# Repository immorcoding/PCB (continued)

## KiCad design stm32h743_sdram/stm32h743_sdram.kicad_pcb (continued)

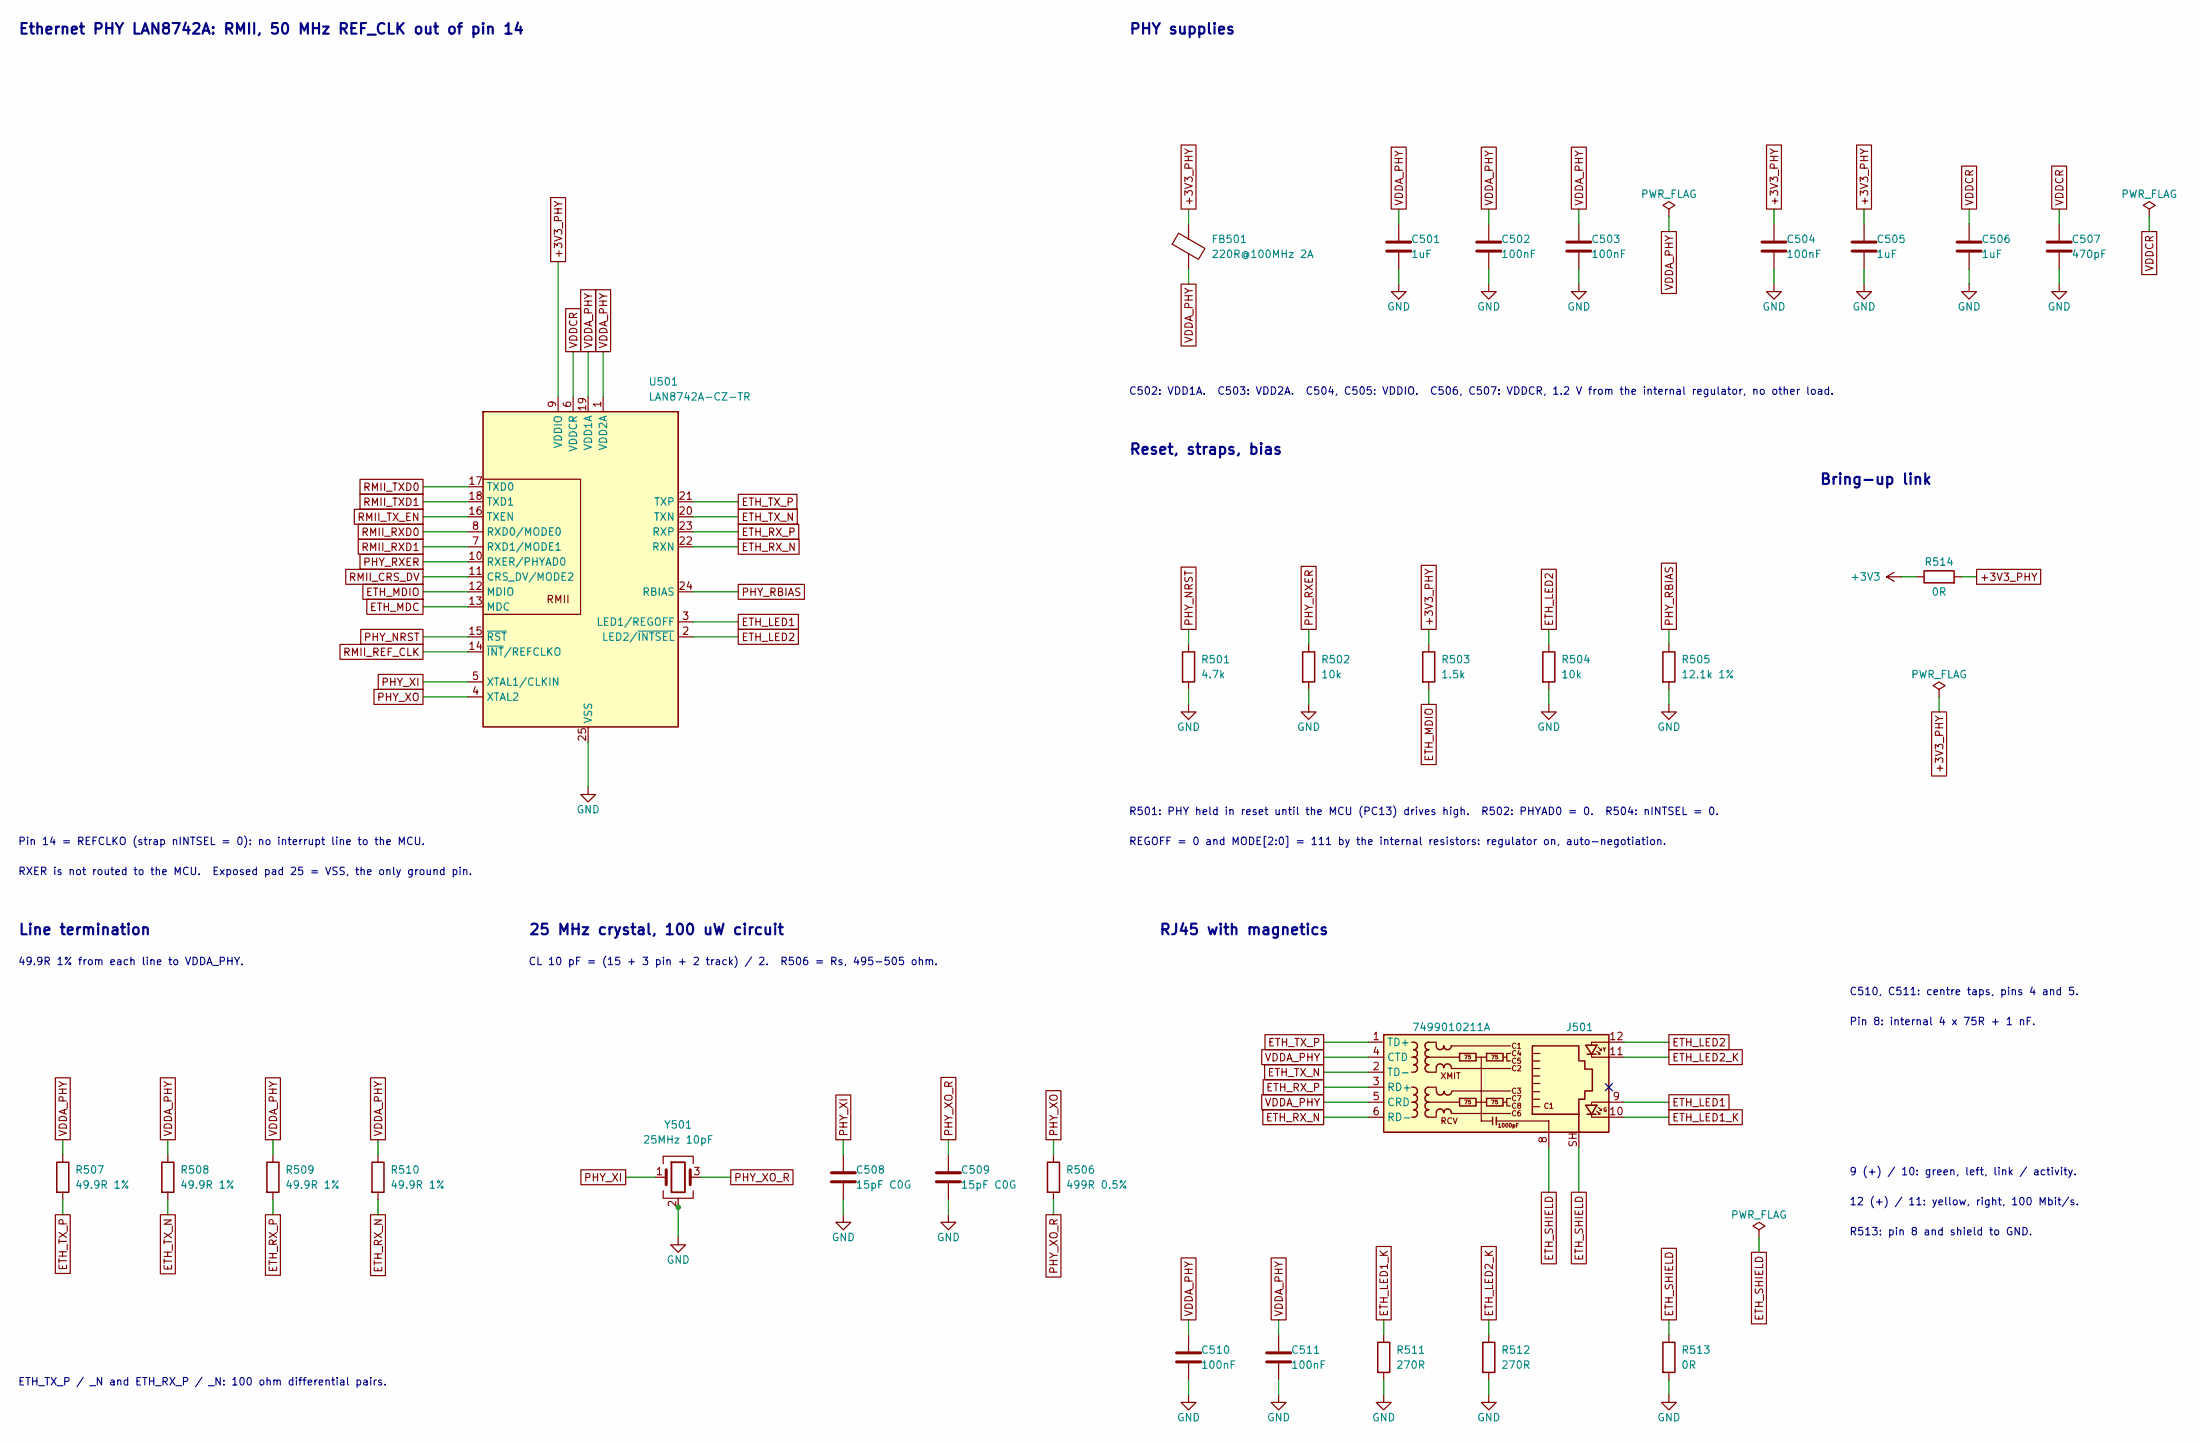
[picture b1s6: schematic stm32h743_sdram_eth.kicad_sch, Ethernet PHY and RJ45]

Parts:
C501, C505, C506: 1uF; C_0603_1608Metric
C502, C503, C504, C510, C511: 100nF; C_0402_1005Metric
C507: 470pF; C_0402_1005Metric
C508, C509: 15pF C0G; C_0402_1005Metric
FB501: 220R@100MHz 2A; L_0603_1608Metric; MPN MH1608-221Y
J501: 7499010211A; RJ45_Wuerth_7499010211A_Horizontal; MPN 7499010211A
R501: 4.7k; R_0402_1005Metric
R502, R504: 10k; R_0402_1005Metric
R503: 1.5k; R_0402_1005Metric
R505: 12.1k 1%; R_0402_1005Metric
R506: 499R 0.5%; R_0402_1005Metric
R507, R508, R509, R510: 49.9R 1%; R_0402_1005Metric
R511, R512: 270R; R_0402_1005Metric
R513: 0R; R_0805_2012Metric
R514: 0R; R_0805_2012Metric; Rating jumper, 2 A or more
U501: LAN8742A-CZ-TR; VQFN-24-1EP_4x4mm_P0.5mm_EP2.5x2.5mm_ThermalVias; MPN LAN8742A-CZ-TR
Y501: 25MHz 10pF; Crystal_SMD_3225-4Pin_3.2x2.5mm; MPN ABM8-25.000MHZ-10-D2X-T

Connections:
+3V3: R514.1; also elsewhere on the board
+3V3_PHY: C504.1, C505.1, FB501.1, R503.1, R514.2, U501.9 (VDDIO)
ETH_LED1: J501.9, U501.3 (LED1/REGOFF)
ETH_LED1_K: J501.10, R511.1
ETH_LED2: J501.12, R504.1, U501.2 (LED2/~INTSEL)
ETH_LED2_K: J501.11, R512.1
ETH_MDC: U501.13 (MDC); also elsewhere on the board
ETH_MDIO: R503.2, U501.12 (MDIO); also elsewhere on the board
ETH_RX_N: J501.6 (RD-), R510.2, U501.22 (RXN)
ETH_RX_P: J501.3 (RD+), R509.2, U501.23 (RXP)
ETH_SHIELD: J501.8, J501.SH, R513.1
ETH_TX_N: J501.2 (TD-), R508.2, U501.20 (TXN)
ETH_TX_P: J501.1 (TD+), R507.2, U501.21 (TXP)
GND: C501.2, C502.2, C503.2, C504.2, C505.2, C506.2, C507.2, C508.2, C509.2, C510.2, C511.2, R501.2, R502.2, R504.2, R505.2, R511.2, R512.2, R513.2, U501.25 (VSS), Y501.2 (G), Y501.4 (G); also elsewhere on the board
PHY_NRST: R501.1, U501.15 (~RST); also elsewhere on the board
PHY_RBIAS: R505.1, U501.24 (RBIAS)
PHY_RXER: R502.1, U501.10 (RXER/PHYAD0)
PHY_XI: C508.1, U501.5 (XTAL1/CLKIN), Y501.1
PHY_XO: R506.1, U501.4 (XTAL2)
PHY_XO_R: C509.1, R506.2, Y501.3
RMII_CRS_DV: U501.11 (CRS_DV/MODE2); also elsewhere on the board
RMII_REF_CLK: U501.14 (~INT/REFCLKO); also elsewhere on the board
RMII_RXD0: U501.8 (RXD0/MODE0); also elsewhere on the board
RMII_RXD1: U501.7 (RXD1/MODE1); also elsewhere on the board
RMII_TXD0: U501.17 (TXD0); also elsewhere on the board
RMII_TXD1: U501.18 (TXD1); also elsewhere on the board
RMII_TX_EN: U501.16 (TXEN); also elsewhere on the board
VDDA_PHY: C501.1, C502.1, C503.1, C510.1, C511.1, FB501.2, J501.4 (CTD), J501.5 (CRD), R507.1, R508.1, R509.1, R510.1, U501.1 (VDD2A), U501.19 (VDD1A)
VDDCR: C506.1, C507.1, U501.6 (VDDCR)

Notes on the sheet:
C510, C511: centre taps, pins 4 and 5.
Pin 14 = REFCLKO (strap nINTSEL = 0): no interrupt line to the MCU.
Reset, straps, bias
C502: VDD1A. C503: VDD2A. C504, C505: VDDIO. C506, C507: VDDCR, 1.2 V from the internal regulator, no other load.
R501: PHY held in reset until the MCU (PC13) drives high. R502: PHYAD0 = 0. R504: nINTSEL = 0.
PHY supplies
Line termination
12 (+) / 11: yellow, right, 100 Mbit/s.
25 MHz crystal, 100 uW circuit
49.9R 1% from each line to VDDA_PHY.
Ethernet PHY LAN8742A: RMII, 50 MHz REF_CLK out of pin 14
RXER is not routed to the MCU. Exposed pad 25 = VSS, the only ground pin.
REGOFF = 0 and MODE[2:0] = 111 by the internal resistors: regulator on, auto-negotiation.
RJ45 with magnetics
Pin 8: internal 4 x 75R + 1 nF.
Bring-up link
9 (+) / 10: green, left, link / activity.
R513: pin 8 and shield to GND.
CL 10 pF = (15 + 3 pin + 2 track) / 2. R506 = Rs, 495-505 ohm.
ETH_TX_P / _N and ETH_RX_P / _N: 100 ohm differential pairs.

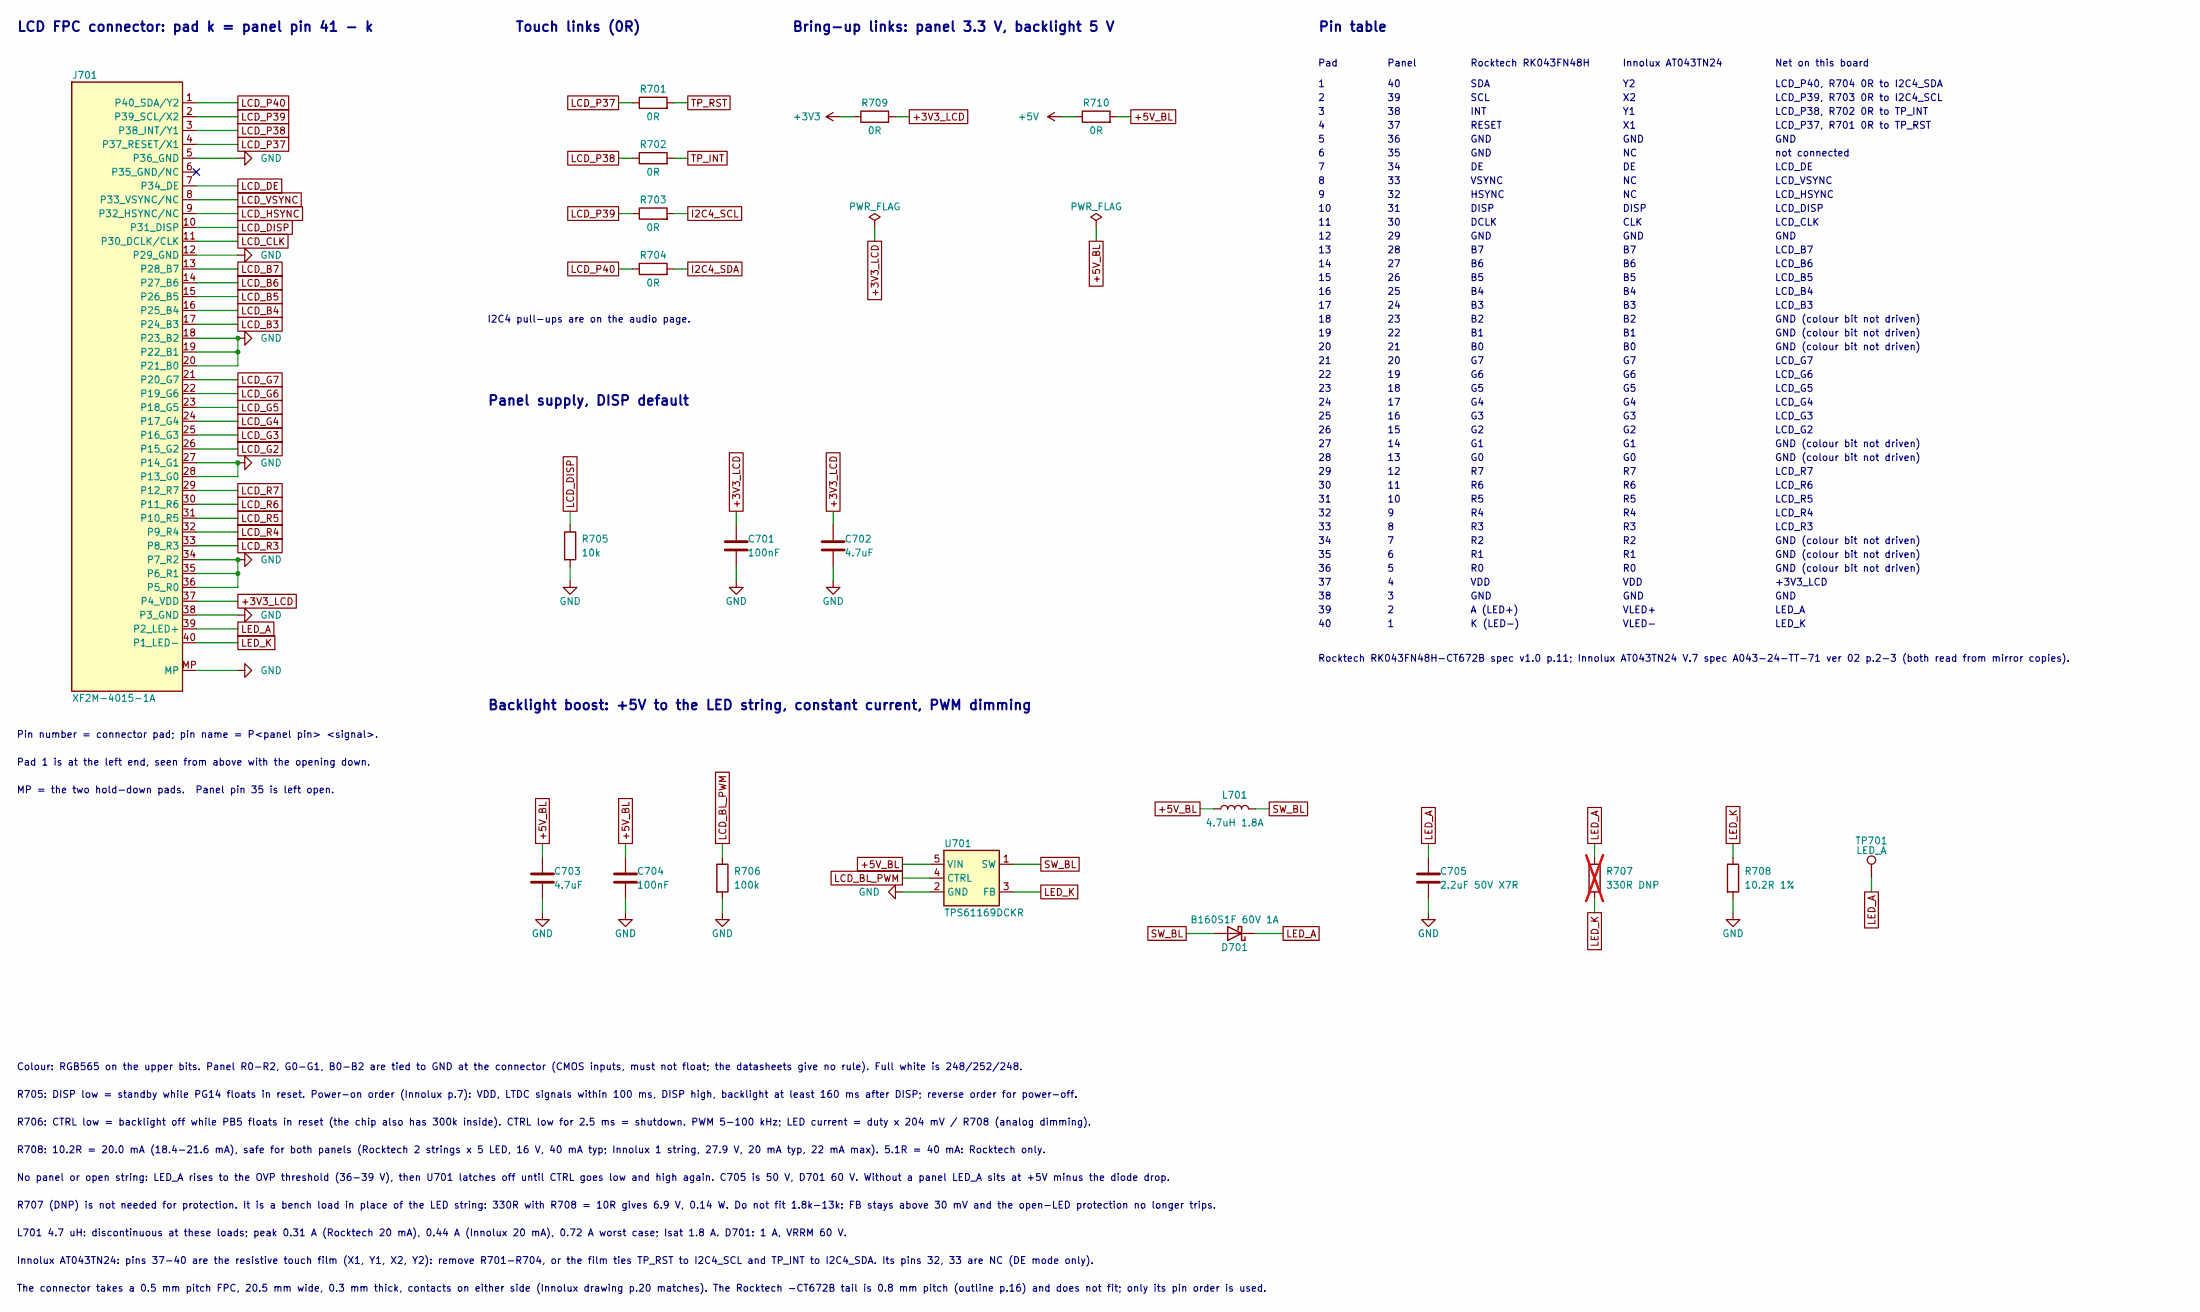
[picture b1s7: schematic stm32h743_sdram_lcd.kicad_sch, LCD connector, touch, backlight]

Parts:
C701, C704: 100nF; C_0402_1005Metric
C702, C703: 4.7uF; C_0603_1608Metric
C705: 2.2uF 50V X7R; C_1206_3216Metric
D701: B160S1F 60V 1A; D_SOD-123F; MPN B160S1F-7
J701: XF2M-4015-1A; Omron_XF2M-4015-1A_1x40-1MP_P0.5mm_Horizontal; MPN XF2M-4015-1A
L701: 4.7uH 1.8A; L_Coilcraft_LPS4018; MPN LPS4018-472MRC
R701, R702, R703, R704: 0R; R_0402_1005Metric
R705: 10k; R_0402_1005Metric
R706: 100k; R_0402_1005Metric
R707: 330R DNP; R_1206_3216Metric; not fitted
R708: 10.2R 1%; R_0603_1608Metric
R709: 0R; R_0603_1608Metric; Rating jumper, 1 A or more
R710: 0R; R_0805_2012Metric; Rating jumper, 2 A or more
TP701: LED_A; TestPoint_Pad_D1.5mm
U701: TPS61169DCKR; SOT-353_SC-70-5; MPN TPS61169DCKR

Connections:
+3V3: R709.1; also elsewhere on the board
+3V3_LCD: C701.1, C702.1, J701.37 (P4_VDD), R709.2
+5V: R710.1; also elsewhere on the board
+5V_BL: C703.1, C704.1, L701.1, R710.2, U701.5 (VIN)
GND: C701.2, C702.2, C703.2, C704.2, C705.2, J701.5 (P36_GND), J701.12 (P29_GND), J701.18 (P23_B2), J701.19 (P22_B1), J701.20 (P21_B0), J701.27 (P14_G1), J701.28 (P13_G0), J701.34 (P7_R2), J701.35 (P6_R1), J701.36 (P5_R0), J701.38 (P3_GND), J701.MP, R705.2, R706.2, R708.2, U701.2 (GND); also elsewhere on the board
I2C4_SCL: R703.2; also elsewhere on the board
I2C4_SDA: R704.2; also elsewhere on the board
LCD_B3: J701.17 (P24_B3); also elsewhere on the board
LCD_B4: J701.16 (P25_B4); also elsewhere on the board
LCD_B5: J701.15 (P26_B5); also elsewhere on the board
LCD_B6: J701.14 (P27_B6); also elsewhere on the board
LCD_B7: J701.13 (P28_B7); also elsewhere on the board
LCD_BL_PWM: R706.1, U701.4 (CTRL); also elsewhere on the board
LCD_CLK: J701.11 (P30_DCLK/CLK); also elsewhere on the board
LCD_DE: J701.7 (P34_DE); also elsewhere on the board
LCD_DISP: J701.10 (P31_DISP), R705.1; also elsewhere on the board
LCD_G2: J701.26 (P15_G2); also elsewhere on the board
LCD_G3: J701.25 (P16_G3); also elsewhere on the board
LCD_G4: J701.24 (P17_G4); also elsewhere on the board
LCD_G5: J701.23 (P18_G5); also elsewhere on the board
LCD_G6: J701.22 (P19_G6); also elsewhere on the board
LCD_G7: J701.21 (P20_G7); also elsewhere on the board
LCD_HSYNC: J701.9 (P32_HSYNC/NC); also elsewhere on the board
LCD_P37: J701.4 (P37_RESET/X1), R701.1
LCD_P38: J701.3 (P38_INT/Y1), R702.1
LCD_P39: J701.2 (P39_SCL/X2), R703.1
LCD_P40: J701.1 (P40_SDA/Y2), R704.1
LCD_R3: J701.33 (P8_R3); also elsewhere on the board
LCD_R4: J701.32 (P9_R4); also elsewhere on the board
LCD_R5: J701.31 (P10_R5); also elsewhere on the board
LCD_R6: J701.30 (P11_R6); also elsewhere on the board
LCD_R7: J701.29 (P12_R7); also elsewhere on the board
LCD_VSYNC: J701.8 (P33_VSYNC/NC); also elsewhere on the board
LED_A: C705.1, D701.1 (K), J701.39 (P2_LED+), R707.1, TP701.1
LED_K: J701.40 (P1_LED-), R707.2, R708.1, U701.3 (FB)
SW_BL: D701.2 (A), L701.2, U701.1 (SW)
TP_INT: R702.2; also elsewhere on the board
TP_RST: R701.2; also elsewhere on the board

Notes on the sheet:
GND
+3V3_LCD
LCD_P39, R703 0R to I2C4_SCL
not connected
Bring-up links: panel 3.3 V, backlight 5 V
DCLK
Rocktech RK043FN48H-CT672B spec v1.0 p.11; Innolux AT043TN24 V.7 spec A043-24-TT-71 ver 02 p.2-3 (both read from mirror copies).
LED_A
LCD_R6
VDD
VSYNC
Pin table
GND (colour bit not driven)
LCD_R4
LCD_HSYNC
INT
LCD_G7
No panel or open string: LED_A rises to the OVP threshold (36-39 V), then U701 latches off until CTRL goes low and high again. C705 is 50 V, D701 60 V. Without a panel LED_A sits at +5V minus the diode drop.
LCD_DISP
LCD_B7
LCD_G3
R706: CTRL low = backlight off while PB5 floats in reset (the chip also has 300k inside). CTRL low for 2.5 ms = shutdown. PWM 5-100 kHz; LED current = duty x 204 mV / R708 (analog dimming).
MP = the two hold-down pads. Panel pin 35 is left open.
LCD_VSYNC
Innolux AT043TN24: pins 37-40 are the resistive touch film (X1, Y1, X2, Y2): remove R701-R704, or the film ties TP_RST to I2C4_SCL and TP_INT to I2C4_SDA. Its pins 32, 33 are NC (DE mode only).
LCD_G6
Colour: RGB565 on the upper bits. Panel R0-R2, G0-G1, B0-B2 are tied to GND at the connector (CMOS inputs, must not float; the datasheets give no rule). Full white is 248/252/248.
LCD_B6
R707 (DNP) is not needed for protection. It is a bench load in place of the LED string: 330R with R708 = 10R gives 6.9 V, 0.14 W. Do not fit 1.8k-13k: FB stays above 30 mV and the open-LED protection no longer trips.
A (LED+)
LCD FPC connector: pad k = panel pin 41 - k
LCD_B3
LED_K
LCD_R7
LCD_G4
I2C4 pull-ups are on the audio page.
SCL
Backlight boost: +5V to the LED string, constant current, PWM dimming
LCD_P38, R702 0R to TP_INT
LCD_G2

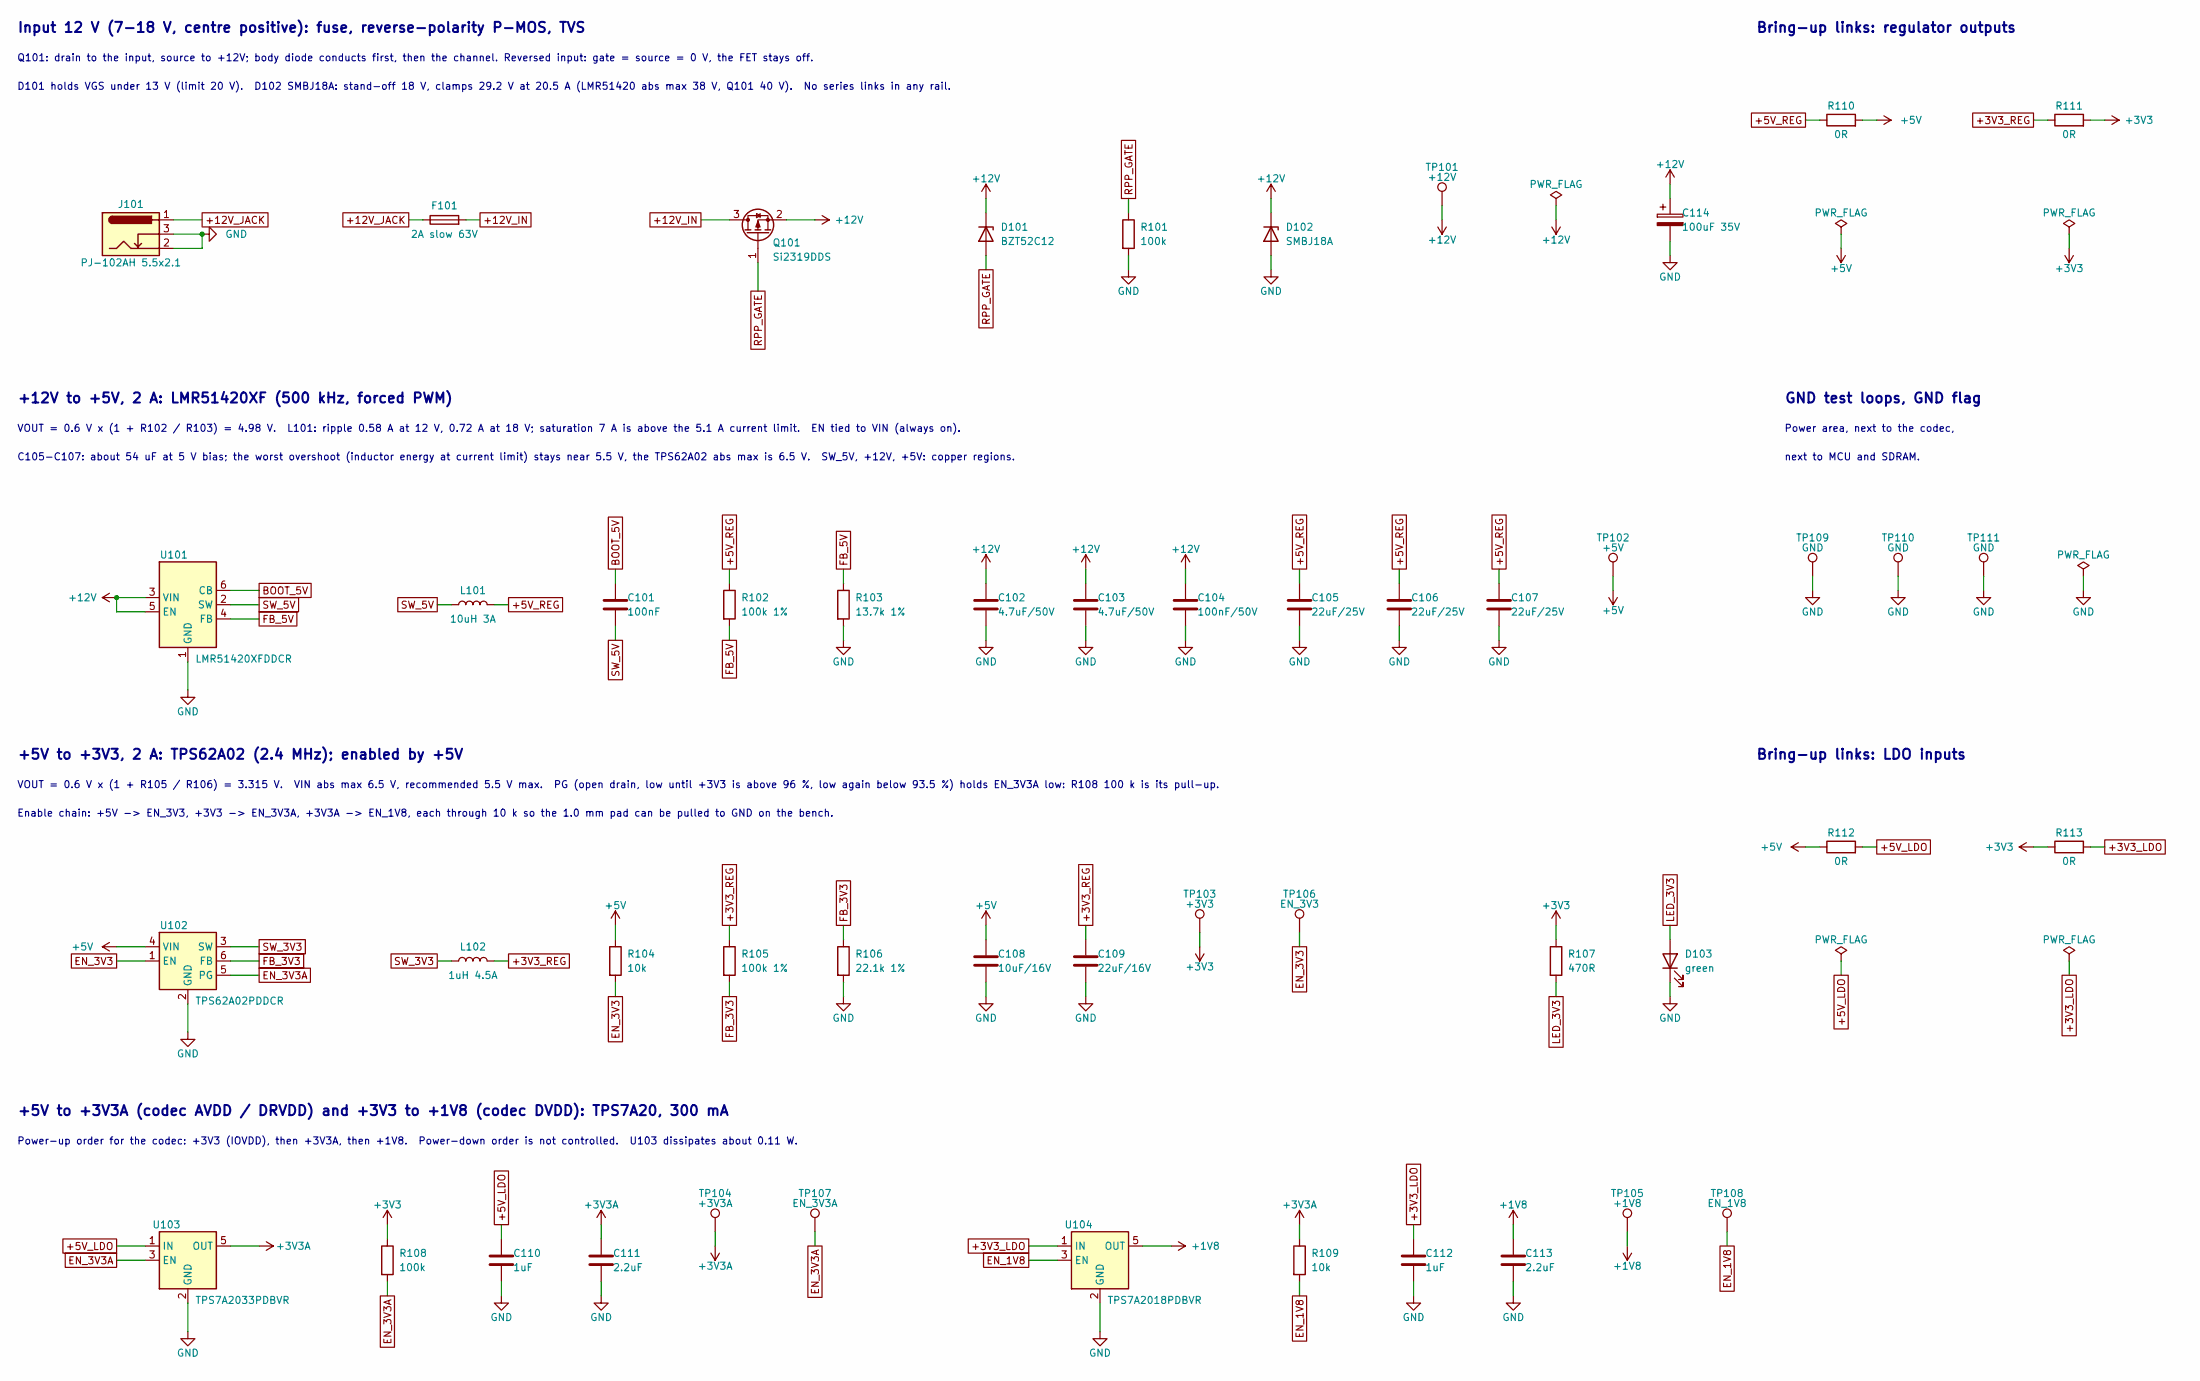
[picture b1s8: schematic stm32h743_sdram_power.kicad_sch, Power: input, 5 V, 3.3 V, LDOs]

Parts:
C101: 100nF; C_0402_1005Metric; Rating X7R 25V
C102, C103: 4.7uF/50V; C_1206_3216Metric; Rating X7R 50V
C104: 100nF/50V; C_0603_1608Metric; Rating X7R 50V
C105, C106, C107: 22uF/25V; C_1210_3225Metric; Rating X7R 25V
C108: 10uF/16V; C_0805_2012Metric; Rating X7R 16V
C109: 22uF/16V; C_1206_3216Metric; Rating X7R or X5R 16V
C110, C112: 1uF; C_0603_1608Metric; Rating X7R 10V
C111, C113: 2.2uF; C_0603_1608Metric; Rating X7R 10V
C114: 100uF 35V; CP_Elec_6.3x7.7; Rating aluminium electrolytic, 35 V
D101: BZT52C12; D_SOD-123; MPN BZT52C12-E3-08
D102: SMBJ18A; D_SMB; MPN SMBJ18A-E3/52
D103: green; LED_0603_1608Metric; MPN VLMG1300-GS08
F101: 2A slow 63V; Fuse_1206_3216Metric; MPN SF-1206S200-2
J101: PJ-102AH 5.5x2.1; BarrelJack_CUI_PJ-102AH_Horizontal; MPN PJ-102AH
L101: 10uH 3A; L_Vishay_IHLP-2525; MPN IHLP2525CZER100M01
L102: 1uH 4.5A; L_Vishay_IHLP-1616; MPN IHLP1616BZER1R0M11
Q101: Si2319DDS; SOT-23; MPN Si2319DDS-T1-GE3
R101, R108: 100k; R_0402_1005Metric
R102, R105: 100k 1%; R_0402_1005Metric
R103: 13.7k 1%; R_0402_1005Metric
R104, R109: 10k; R_0402_1005Metric
R106: 22.1k 1%; R_0402_1005Metric
R107: 470R; R_0402_1005Metric
R110, R111: 0R; R_1206_3216Metric; Rating jumper, 2 A or more
R112, R113: 0R; R_0805_2012Metric; Rating jumper, 2 A or more
TP101: +12V; TestPoint_Pad_D1.5mm
TP102: +5V; TestPoint_Pad_D1.5mm
TP103: +3V3; TestPoint_Pad_D1.5mm
TP104: +3V3A; TestPoint_Pad_D1.5mm
TP105: +1V8; TestPoint_Pad_D1.5mm
TP106: EN_3V3; TestPoint_Pad_D1.0mm
TP107: EN_3V3A; TestPoint_Pad_D1.0mm
TP108: EN_1V8; TestPoint_Pad_D1.0mm
TP109, TP110, TP111: GND; TestPoint_Loop_D2.50mm_Drill1.0mm; MPN 5001
U101: LMR51420XFDDCR; SOT-23-6; MPN LMR51420XFDDCR
U102: TPS62A02PDDCR; SOT-23-6; MPN TPS62A02PDDCR
U103: TPS7A2033PDBVR; SOT-23-5; MPN TPS7A2033PDBVR
U104: TPS7A2018PDBVR; SOT-23-5; MPN TPS7A2018PDBVR

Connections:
+1V8: C113.1, TP105.1, U104.5 (OUT); also elsewhere on the board
+3V3: R107.1, R108.1, R111.2, R113.1, TP103.1; also elsewhere on the board
+3V3A: C111.1, R109.1, TP104.1, U103.5 (OUT); also elsewhere on the board
+3V3_LDO: C112.1, R113.2, U104.1 (IN)
+3V3_REG: C109.1, L102.2, R105.1, R111.1
+5V: C108.1, R104.1, R110.2, R112.1, TP102.1, U102.4 (VIN); also elsewhere on the board
+5V_LDO: C110.1, R112.2, U103.1 (IN)
+5V_REG: C105.1, C106.1, C107.1, L101.2, R102.1, R110.1
+12V: C102.1, C103.1, C104.1, C114.1, D101.1 (K), D102.1 (K), Q101.2 (S), TP101.1, U101.3 (VIN), U101.5 (EN)
+12V_IN: F101.2, Q101.3 (D)
+12V_JACK: F101.1, J101.1
BOOT_5V: C101.1, U101.6 (CB)
EN_1V8: R109.2, TP108.1, U104.3 (EN)
EN_3V3: R104.2, TP106.1, U102.1 (EN)
EN_3V3A: R108.2, TP107.1, U102.5 (PG), U103.3 (EN)
FB_3V3: R105.2, R106.1, U102.6 (FB)
FB_5V: R102.2, R103.1, U101.4 (FB)
GND: C102.2, C103.2, C104.2, C105.2, C106.2, C107.2, C108.2, C109.2, C110.2, C111.2, C112.2, C113.2, C114.2, D102.2 (A), D103.1 (K), J101.2, J101.3, R101.2, R103.2, R106.2, TP109.1, TP110.1, TP111.1, U101.1 (GND), U102.2 (GND), U103.2 (GND), U104.2 (GND); also elsewhere on the board
LED_3V3: D103.2 (A), R107.2
RPP_GATE: D101.2 (A), Q101.1 (G), R101.1
SW_3V3: L102.1, U102.3 (SW)
SW_5V: C101.2, L101.1, U101.2 (SW)

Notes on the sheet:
VOUT = 0.6 V x (1 + R105 / R106) = 3.315 V. VIN abs max 6.5 V, recommended 5.5 V max. PG (open drain, low until +3V3 is above 96 %, low again below 93.5 %) holds EN_3V3A low: R108 100 k is its pull-up.
Power-up order for the codec: +3V3 (IOVDD), then +3V3A, then +1V8. Power-down order is not controlled. U103 dissipates about 0.11 W.
Power area, next to the codec,
GND test loops, GND flag
C105-C107: about 54 uF at 5 V bias; the worst overshoot (inductor energy at current limit) stays near 5.5 V, the TPS62A02 abs max is 6.5 V. SW_5V, +12V, +5V: copper regions.
+12V to +5V, 2 A: LMR51420XF (500 kHz, forced PWM)
D101 holds VGS under 13 V (limit 20 V). D102 SMBJ18A: stand-off 18 V, clamps 29.2 V at 20.5 A (LMR51420 abs max 38 V, Q101 40 V). No series links in any rail.
Enable chain: +5V -> EN_3V3, +3V3 -> EN_3V3A, +3V3A -> EN_1V8, each through 10 k so the 1.0 mm pad can be pulled to GND on the bench.
+5V to +3V3A (codec AVDD / DRVDD) and +3V3 to +1V8 (codec DVDD): TPS7A20, 300 mA
Bring-up links: LDO inputs
next to MCU and SDRAM.
Q101: drain to the input, source to +12V; body diode conducts first, then the channel. Reversed input: gate = source = 0 V, the FET stays off.
+5V to +3V3, 2 A: TPS62A02 (2.4 MHz); enabled by +5V
Input 12 V (7-18 V, centre positive): fuse, reverse-polarity P-MOS, TVS
Bring-up links: regulator outputs
VOUT = 0.6 V x (1 + R102 / R103) = 4.98 V. L101: ripple 0.58 A at 12 V, 0.72 A at 18 V; saturation 7 A is above the 5.1 A current limit. EN tied to VIN (always on).

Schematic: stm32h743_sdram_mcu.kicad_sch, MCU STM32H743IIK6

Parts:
C201, C202, C203, C204, C205, C206, C207, C208, C209, C210, C211, C212, C213, C214, C215, C220, C222, C224: 100nF; C_0402_1005Metric
C216, C221, C223: 1uF; C_0402_1005Metric
C217: 4.7uF; C_0603_1608Metric
C218, C219: 2.2uF; C_0402_1005Metric
C225, C226: 15pF; C_0402_1005Metric
C227, C228: 10pF; C_0402_1005Metric
FB201: 220R@100MHz 2A; L_0603_1608Metric; MPN MH1608-221Y
R201: 33R; R_0402_1005Metric
R202: 10k; R_0402_1005Metric
R203: 0R; R_0805_2012Metric; Rating jumper, 2 A or more
SW201: RESET; SW_SPST_B3U-1000P; MPN B3U-1000P
TP201: BOOT0; TestPoint_Pad_D1.0mm
U201: STM32H743IIK6; UFBGA-201_10x10mm_Layout15x15_P0.65mm; MPN STM32H743IIK6
Y201: 25MHz 10pF; Crystal_SMD_3225-4Pin_3.2x2.5mm; MPN ABM8-25.000MHZ-10-D2X-T
Y202: 32.768kHz 7pF; Crystal_SMD_3215-2Pin_3.2x1.5mm; MPN ABS07-32.768KHZ-7-T

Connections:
+3V3: R203.1; also elsewhere on the board
+3V3_MCU: C201.1, C202.1, C203.1, C204.1, C205.1, C206.1, C207.1, C208.1, C209.1, C210.1, C211.1, C212.1, C213.1, C214.1, C215.1, C216.1, C217.1, FB201.1, R203.2, U201.C1 (VBAT), U201.C5 (VDD), U201.C6 (PDR_ON), U201.C7 (VDD), U201.C8 (VDD), U201.C9 (VDD), U201.F3 (VDD), U201.G3 (VDD), U201.G13 (VDD), U201.H13 (VDD33_USB), U201.J12 (VDD), U201.J13 (VDD), U201.K4 (VDD), U201.N8 (VDD), U201.N9 (VDD), U201.N10 (VDD)
BOOT0: R202.1, TP201.1, U201.D6 (BOOT0)
CAN_STB: U201.C11 (PD5); also elsewhere on the board
CODEC_NRST: U201.C10 (PG9); also elsewhere on the board
ETH_MDC: U201.M3 (PC1); also elsewhere on the board
ETH_MDIO: U201.P2 (PA2); also elsewhere on the board
FDCAN1_RX: U201.C15 (PA11); also elsewhere on the board
FDCAN1_TX: U201.B15 (PA12); also elsewhere on the board
FMC_A0: U201.E2 (PF0); also elsewhere on the board
FMC_A1: U201.H3 (PF1); also elsewhere on the board
FMC_A2: U201.H2 (PF2); also elsewhere on the board
FMC_A3: U201.J2 (PF3); also elsewhere on the board
FMC_A4: U201.J3 (PF4); also elsewhere on the board
FMC_A5: U201.K3 (PF5); also elsewhere on the board
FMC_A6: U201.P6 (PF12); also elsewhere on the board
FMC_A7: U201.N6 (PF13); also elsewhere on the board
FMC_A8: U201.R7 (PF14); also elsewhere on the board
FMC_A9: U201.P7 (PF15); also elsewhere on the board
FMC_A10: U201.N7 (PG0); also elsewhere on the board
FMC_A11: U201.M7 (PG1); also elsewhere on the board
FMC_A12: U201.L15 (PG2); also elsewhere on the board
FMC_BA0: U201.K14 (PG4); also elsewhere on the board
FMC_BA1: U201.K13 (PG5); also elsewhere on the board
FMC_D0: U201.M14 (PD14); also elsewhere on the board
FMC_D1: U201.L14 (PD15); also elsewhere on the board
FMC_D2: U201.B12 (PD0); also elsewhere on the board
FMC_D3: U201.C12 (PD1); also elsewhere on the board
FMC_D4: U201.R8 (PE7); also elsewhere on the board
FMC_D5: U201.P8 (PE8); also elsewhere on the board
FMC_D6: U201.P9 (PE9); also elsewhere on the board
FMC_D7: U201.R9 (PE10); also elsewhere on the board
FMC_D8: U201.P10 (PE11); also elsewhere on the board
FMC_D9: U201.R10 (PE12); also elsewhere on the board
FMC_D10: U201.N11 (PE13); also elsewhere on the board
FMC_D11: U201.P11 (PE14); also elsewhere on the board
FMC_D12: U201.R11 (PE15); also elsewhere on the board
FMC_D13: U201.P15 (PD8); also elsewhere on the board
FMC_D14: U201.P14 (PD9); also elsewhere on the board
FMC_D15: U201.N15 (PD10); also elsewhere on the board
FMC_D16: U201.M12 (PH8); also elsewhere on the board
FMC_D17: U201.M13 (PH9); also elsewhere on the board
FMC_D18: U201.L13 (PH10); also elsewhere on the board
FMC_D19: U201.L12 (PH11); also elsewhere on the board
FMC_D20: U201.K12 (PH12); also elsewhere on the board
FMC_D21: U201.E12 (PH13); also elsewhere on the board
FMC_D22: U201.E13 (PH14); also elsewhere on the board
FMC_D23: U201.D13 (PH15); also elsewhere on the board
FMC_D24: U201.E14 (PI0); also elsewhere on the board
FMC_D25: U201.D14 (PI1); also elsewhere on the board
FMC_D26: U201.C14 (PI2); also elsewhere on the board
FMC_D27: U201.C13 (PI3); also elsewhere on the board
FMC_D28: U201.C3 (PI6); also elsewhere on the board
FMC_D29: U201.C2 (PI7); also elsewhere on the board
FMC_D30: U201.D3 (PI9); also elsewhere on the board
FMC_D31: U201.E3 (PI10); also elsewhere on the board
FMC_NBL0: U201.A4 (PE0); also elsewhere on the board
FMC_NBL1: U201.A3 (PE1); also elsewhere on the board
FMC_NBL2: U201.D4 (PI4); also elsewhere on the board
FMC_NBL3: U201.C4 (PI5); also elsewhere on the board
FMC_SDCKE0: U201.F4 (PH2); also elsewhere on the board
FMC_SDCLK: R201.1, U201.H14 (PG8)
FMC_SDCLK_R: R201.2; also elsewhere on the board
FMC_SDNCAS: U201.B7 (PG15); also elsewhere on the board
FMC_SDNE0: U201.G4 (PH3); also elsewhere on the board
FMC_SDNRAS: U201.R6 (PF11); also elsewhere on the board
FMC_SDNWE: U201.J4 (PH5); also elsewhere on the board
GND: C201.2, C202.2, C203.2, C204.2, C205.2, C206.2, C207.2, C208.2, C209.2, C210.2, C211.2, C212.2, C213.2, C214.2, C215.2, C216.2, C217.2, C218.2, C219.2, C220.2, C221.2, C222.2, C223.2, C224.2, C225.2, C226.2, C227.2, C228.2, R202.2, SW201.2, U201.D5 (VSS), U201.D7 (VSS), U201.D8 (VSS), U201.D9 (VSS), U201.F2 (VSS), U201.F6 (VSS), U201.F7 (VSS), U201.F8 (VSS), U201.F9 (VSS), U201.F10 (VSS), U201.F12 (VSS), U201.G2 (VSS), U201.G6 (VSS), U201.G7 (VSS), U201.G8 (VSS), U201.G9 (VSS), U201.G10 (VSS), U201.G12 (VSS), U201.H6 (VSS), U201.H7 (VSS), U201.H8 (VSS), U201.H9 (VSS), U201.H10 (VSS), U201.H12 (VSS), U201.J6 (VSS), U201.J7 (VSS), U201.J8 (VSS), U201.J9 (VSS), U201.J10 (VSS), U201.K6 (VSS), U201.K7 (VSS), U201.K8 (VSS), U201.K9 (VSS), U201.K10 (VSS), U201.L4 (VSS), U201.M1 (VSSA), U201.M8 (VSS), U201.M9 (VSS), U201.N1 (VREF-), Y201.2 (G), Y201.4 (G); also elsewhere on the board
HSE_IN: C225.1, U201.G1 (PH0), Y201.1
HSE_OUT: C226.1, U201.H1, Y201.3
I2C4_SCL: U201.N13 (PD12); also elsewhere on the board
I2C4_SDA: U201.M15 (PD13); also elsewhere on the board
LCD_B3: U201.F15 (PA8); also elsewhere on the board
LCD_B4: U201.D15 (PA10); also elsewhere on the board
LCD_B5: U201.R2 (PA3); also elsewhere on the board
LCD_B6: U201.A5 (PB8); also elsewhere on the board
LCD_B7: U201.B4 (PB9); also elsewhere on the board
LCD_BL_PWM: U201.A6 (PB5); also elsewhere on the board
LCD_CLK: U201.J14 (PG7); also elsewhere on the board
LCD_DE: U201.L1 (PF10); also elsewhere on the board
LCD_DISP: U201.A7 (PG14); also elsewhere on the board
LCD_G2: U201.P3 (PA6); also elsewhere on the board
LCD_G3: U201.B10 (PG10); also elsewhere on the board
LCD_G4: U201.R12 (PB10); also elsewhere on the board
LCD_G5: U201.R13 (PB11); also elsewhere on the board
LCD_G6: U201.G15 (PC7); also elsewhere on the board
LCD_G7: U201.D11 (PD3); also elsewhere on the board
LCD_HSYNC: U201.H15 (PC6); also elsewhere on the board
LCD_R3: U201.R5 (PB0); also elsewhere on the board
LCD_R4: U201.P4 (PA5); also elsewhere on the board
LCD_R5: U201.E15 (PA9); also elsewhere on the board
LCD_R6: U201.R4 (PB1); also elsewhere on the board
LCD_R7: U201.J15 (PG6); also elsewhere on the board
LCD_VSYNC: U201.N4 (PA4); also elsewhere on the board
LED1: U201.M11 (PH6); also elsewhere on the board
LED2: U201.N12 (PH7); also elsewhere on the board
LSE_IN: C227.1, U201.E1 (PC14), Y202.1
LSE_OUT: C228.1, U201.F1 (PC15), Y202.2
NRST: C224.1, SW201.1, U201.J1 (NRST); also elsewhere on the board
PHY_NRST: U201.D1 (PC13); also elsewhere on the board
QSPI_BK1_IO0: U201.L3 (PF8); also elsewhere on the board
QSPI_BK1_IO1: U201.L2 (PF9); also elsewhere on the board
QSPI_BK1_IO2: U201.K1 (PF7); also elsewhere on the board
QSPI_BK1_IO3: U201.K2 (PF6); also elsewhere on the board
QSPI_BK1_NCS: U201.B6; also elsewhere on the board
QSPI_CLK: U201.M6 (PB2); also elsewhere on the board
RMII_CRS_DV: U201.R3 (PA7); also elsewhere on the board
RMII_REF_CLK: U201.N2 (PA1); also elsewhere on the board
RMII_RXD0: U201.N5 (PC4); also elsewhere on the board
RMII_RXD1: U201.P5 (PC5); also elsewhere on the board
RMII_TXD0: U201.A8 (PG13); also elsewhere on the board
RMII_TXD1: U201.B8 (PG12); also elsewhere on the board
RMII_TX_EN: U201.B9 (PG11); also elsewhere on the board
SAI1_FS_A: U201.B1 (PE4); also elsewhere on the board
SAI1_MCLK_A: U201.A2 (PE2); also elsewhere on the board
SAI1_SCK_A: U201.B2 (PE5); also elsewhere on the board
SAI1_SD_A: U201.B3 (PE6); also elsewhere on the board
SAI1_SD_B: U201.A1 (PE3); also elsewhere on the board
SDMMC1_CK: U201.A12 (PC12); also elsewhere on the board
SDMMC1_CMD: U201.D12 (PD2); also elsewhere on the board
SDMMC1_D0: U201.G14 (PC8); also elsewhere on the board
SDMMC1_D1: U201.F14 (PC9); also elsewhere on the board
SDMMC1_D2: U201.B14 (PC10); also elsewhere on the board
SDMMC1_D3: U201.B13 (PC11); also elsewhere on the board
SD_CD: U201.D10 (PD4); also elsewhere on the board
SWCLK: U201.A14; also elsewhere on the board
SWDIO: U201.A15 (PA13); also elsewhere on the board
SWO: U201.A10 (PB3); also elsewhere on the board
TP_INT: U201.K15 (PG3); also elsewhere on the board
TP_RST: U201.N14 (PD11); also elsewhere on the board
USART1_RX: U201.R15 (PB15); also elsewhere on the board
USART1_TX: U201.R14 (PB14); also elsewhere on the board
USER_KEY: U201.N3 (PA0); also elsewhere on the board
VCAP1: C218.1, U201.F13 (VCAP)
VCAP2: C219.1, U201.M10 (VCAP)
VDDA_MCU: C220.1, C221.1, C222.1, C223.1, FB201.2, U201.P1 (VREF+), U201.R1 (VDDA)

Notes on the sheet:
Reset and boot
Bring-up link
HSE 25 MHz
Analog supply: VDDA and VREF+ from +3V3 through a bead
LSE 32.768 kHz
SDCLK series resistor (at the MCU ball)
VDD decoupling: 100 nF per VDD ball (13) + VBAT + VDD33USB, bulk 4.7 uF, 1 uF at VDD33USB
VCAP: 2.2 uF each, ESR < 0.1 Ohm
MCU STM32H743IIK6 (UFBGA176+25): IO from pins.csv, 127 of 140 used, 13 free IOs unconnected
